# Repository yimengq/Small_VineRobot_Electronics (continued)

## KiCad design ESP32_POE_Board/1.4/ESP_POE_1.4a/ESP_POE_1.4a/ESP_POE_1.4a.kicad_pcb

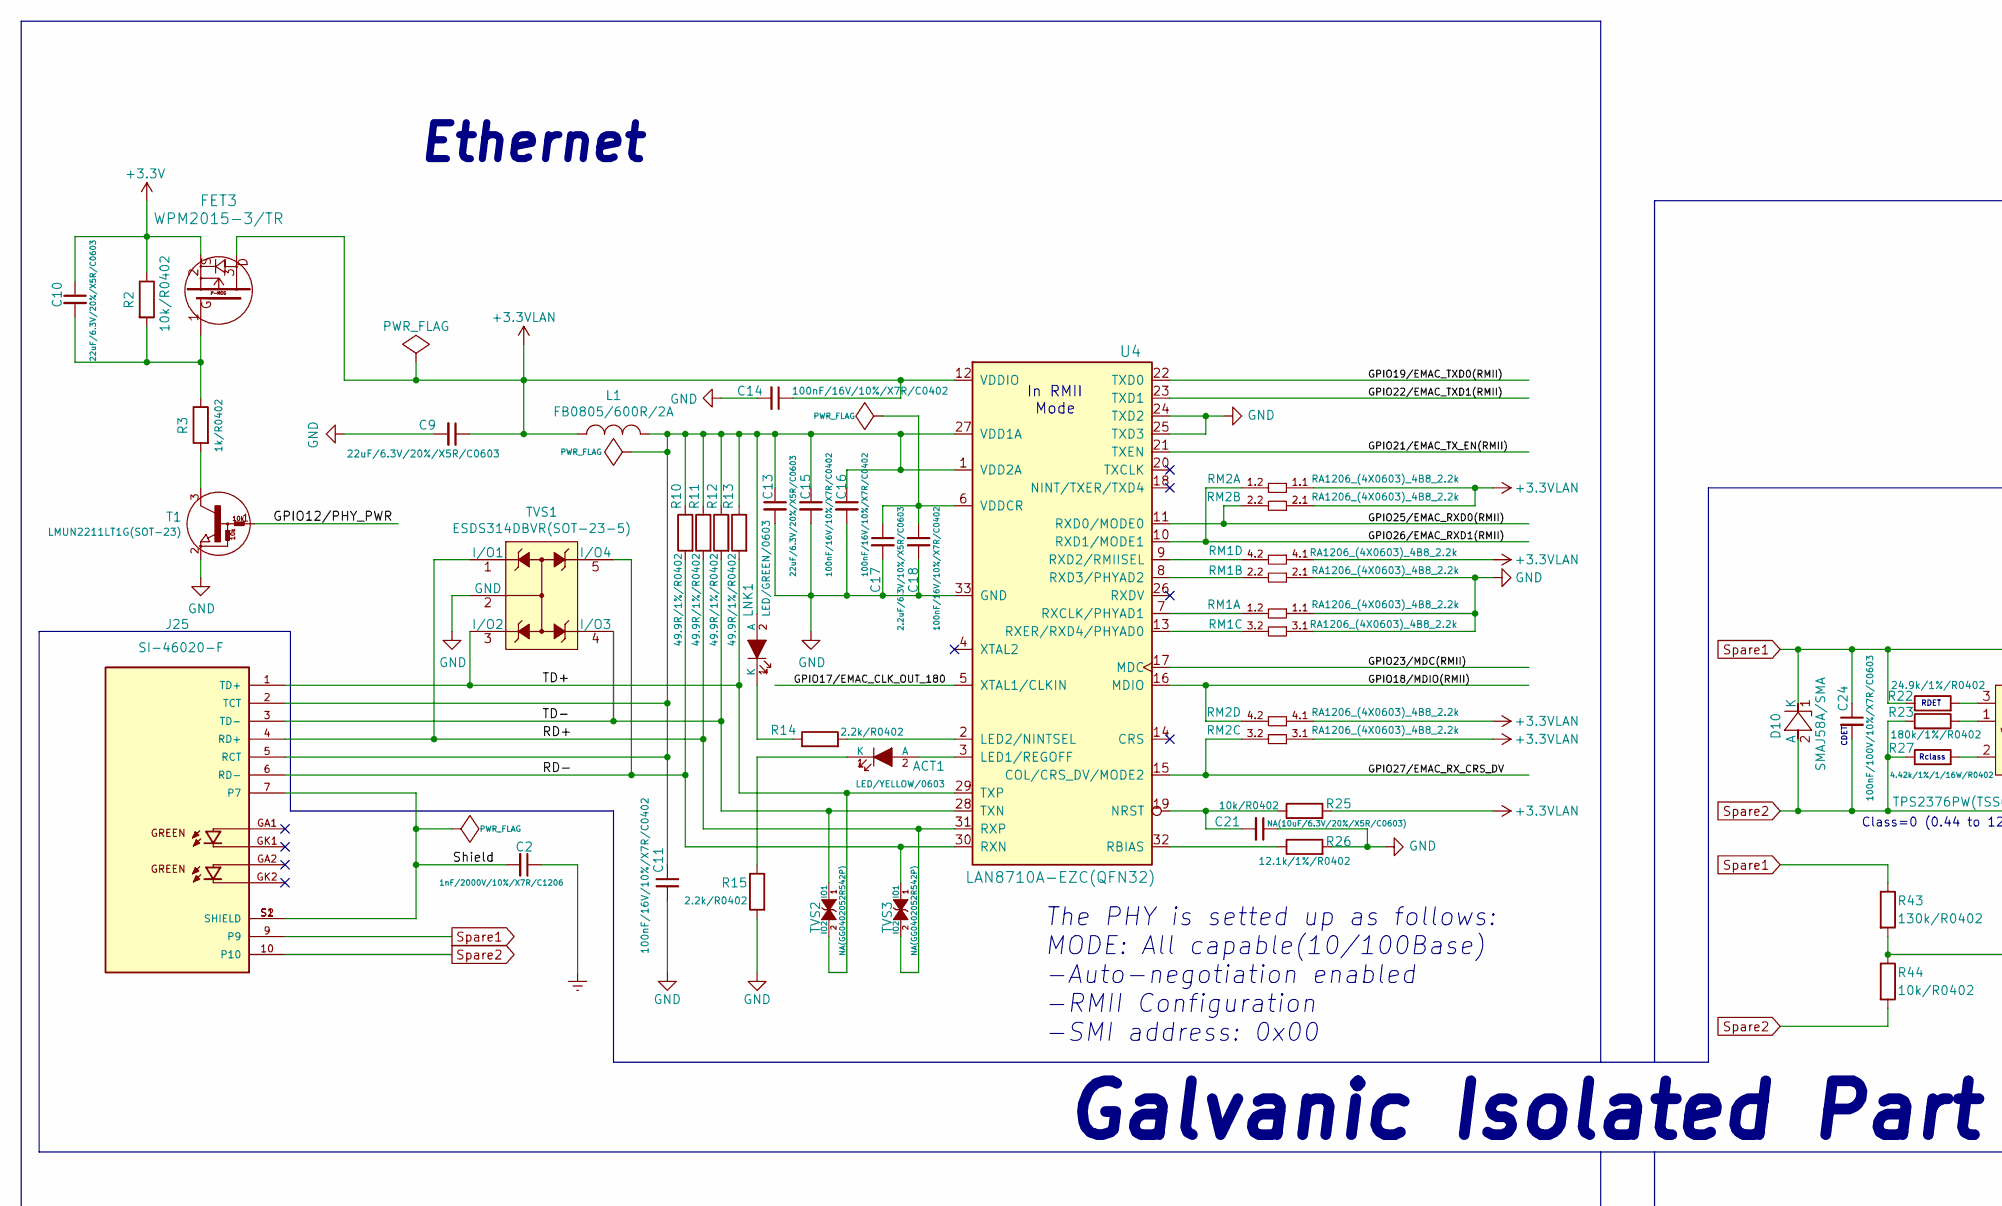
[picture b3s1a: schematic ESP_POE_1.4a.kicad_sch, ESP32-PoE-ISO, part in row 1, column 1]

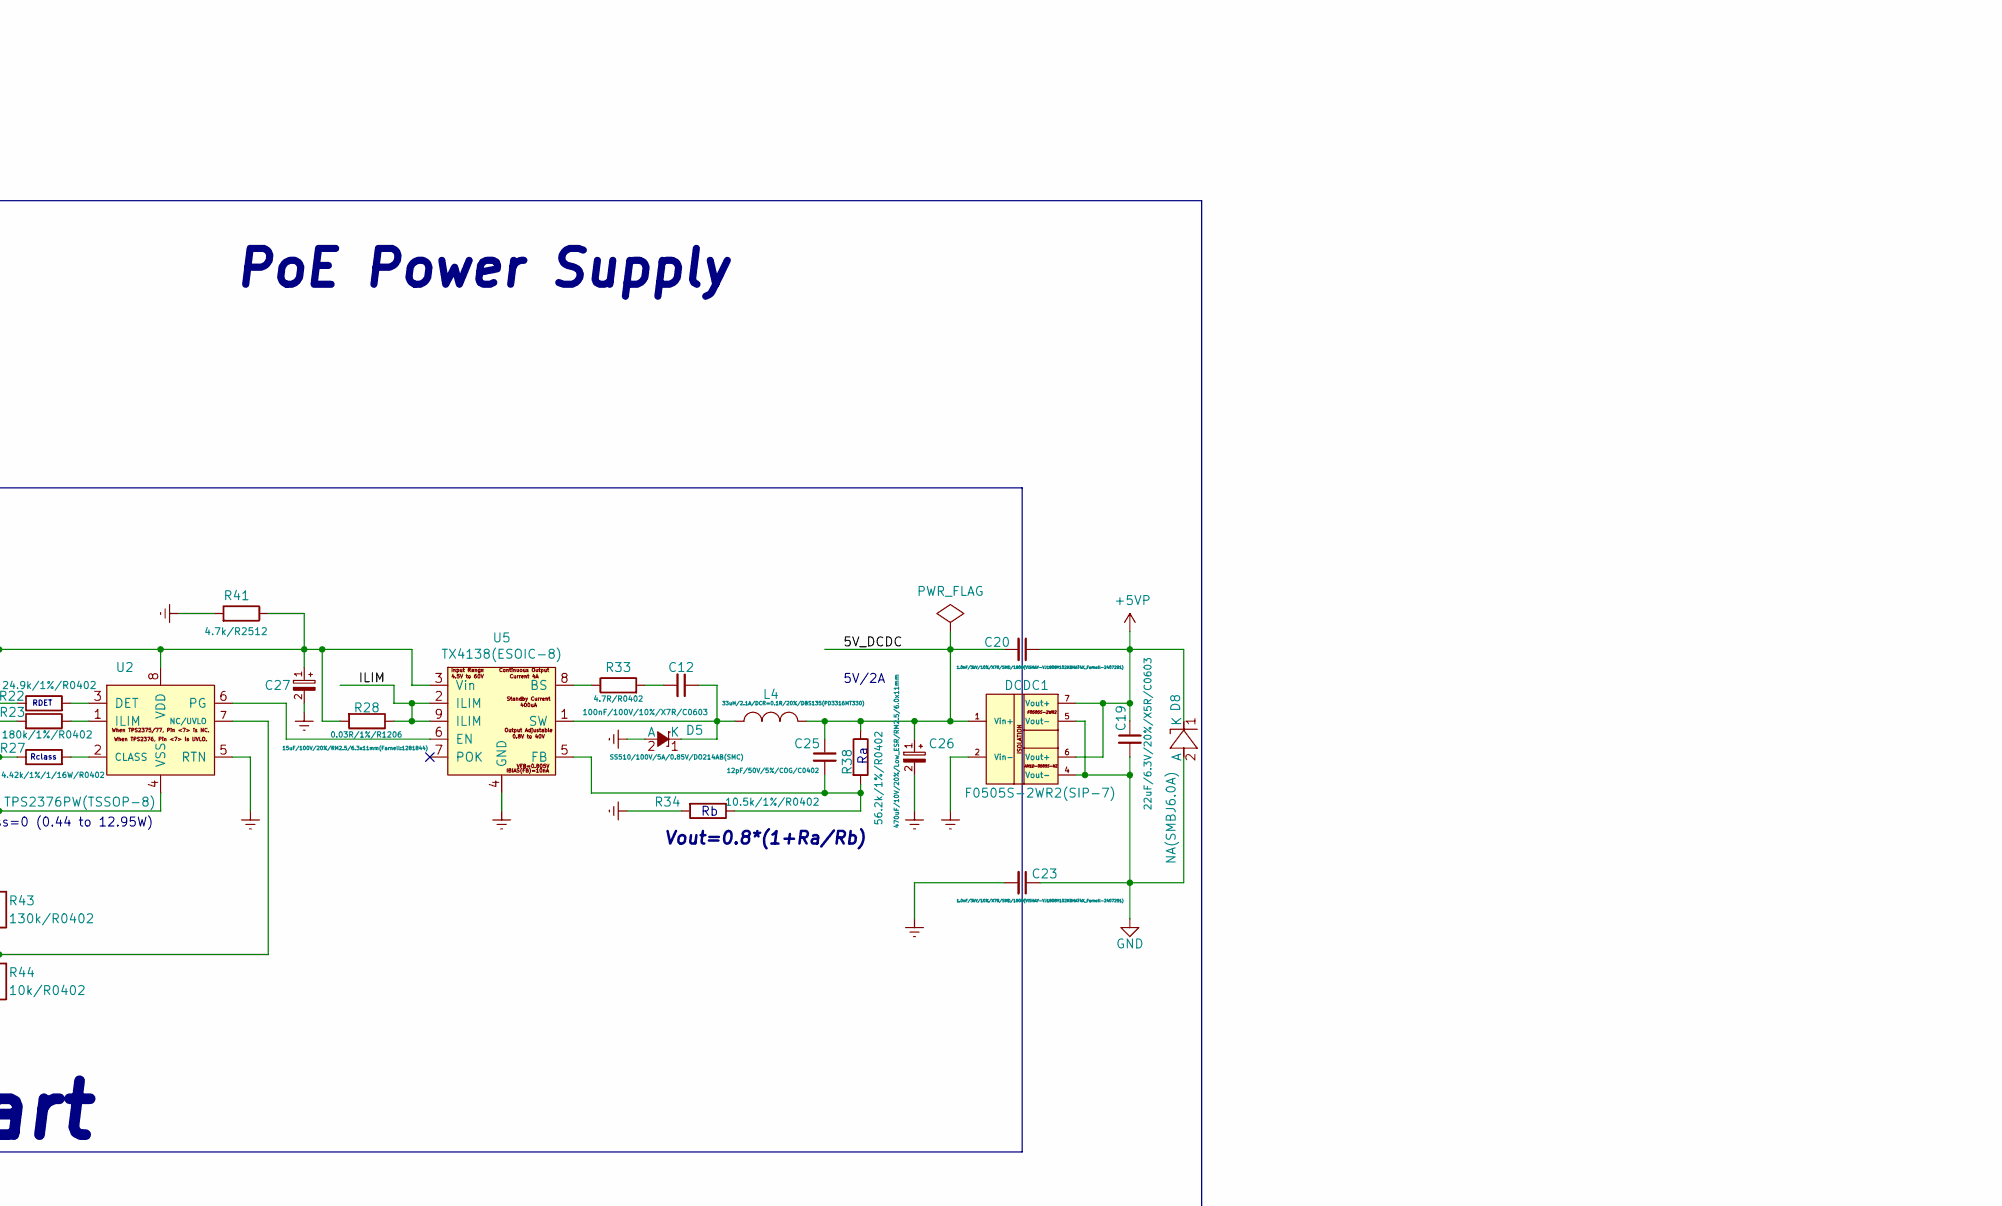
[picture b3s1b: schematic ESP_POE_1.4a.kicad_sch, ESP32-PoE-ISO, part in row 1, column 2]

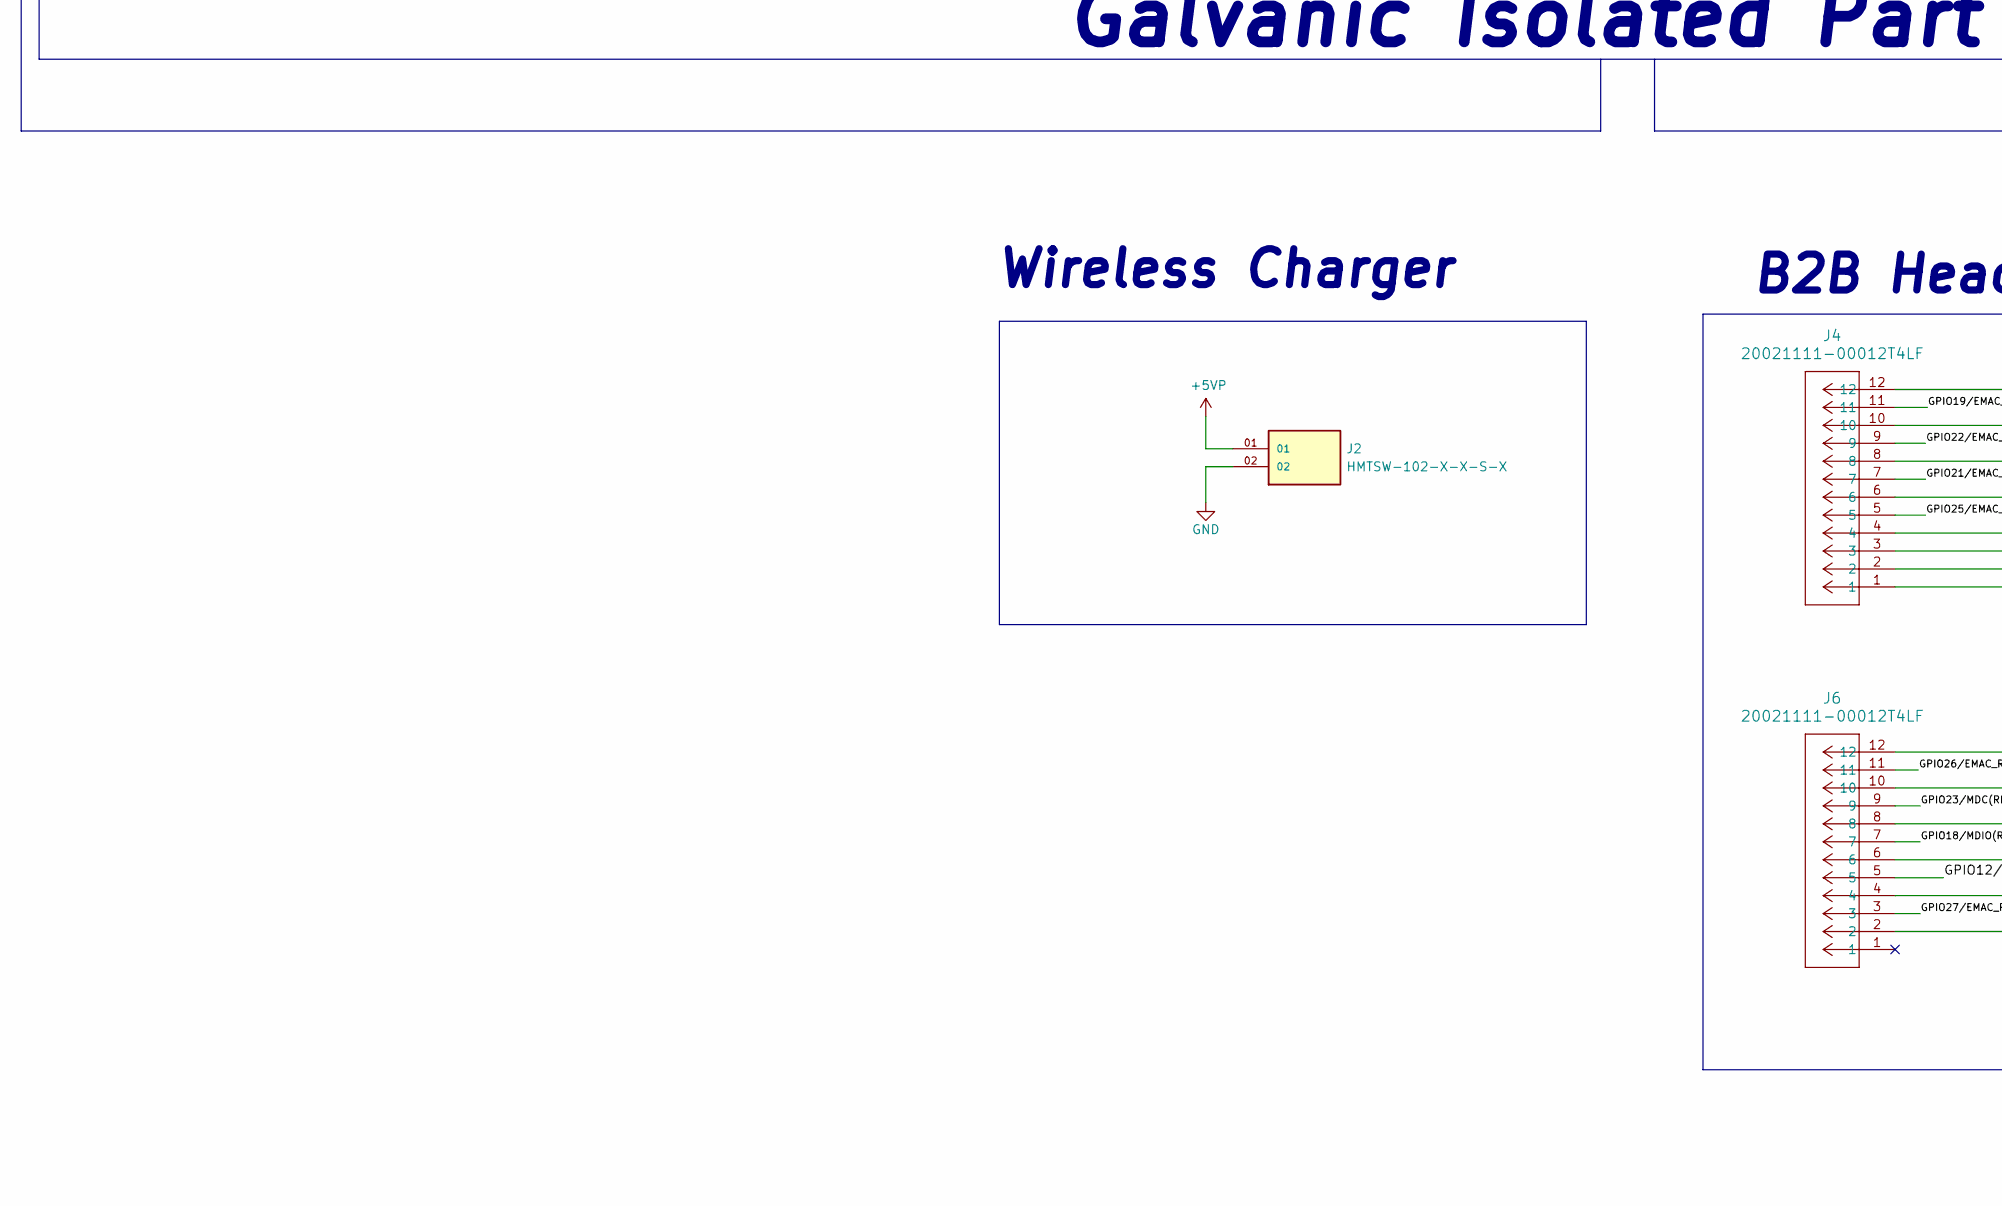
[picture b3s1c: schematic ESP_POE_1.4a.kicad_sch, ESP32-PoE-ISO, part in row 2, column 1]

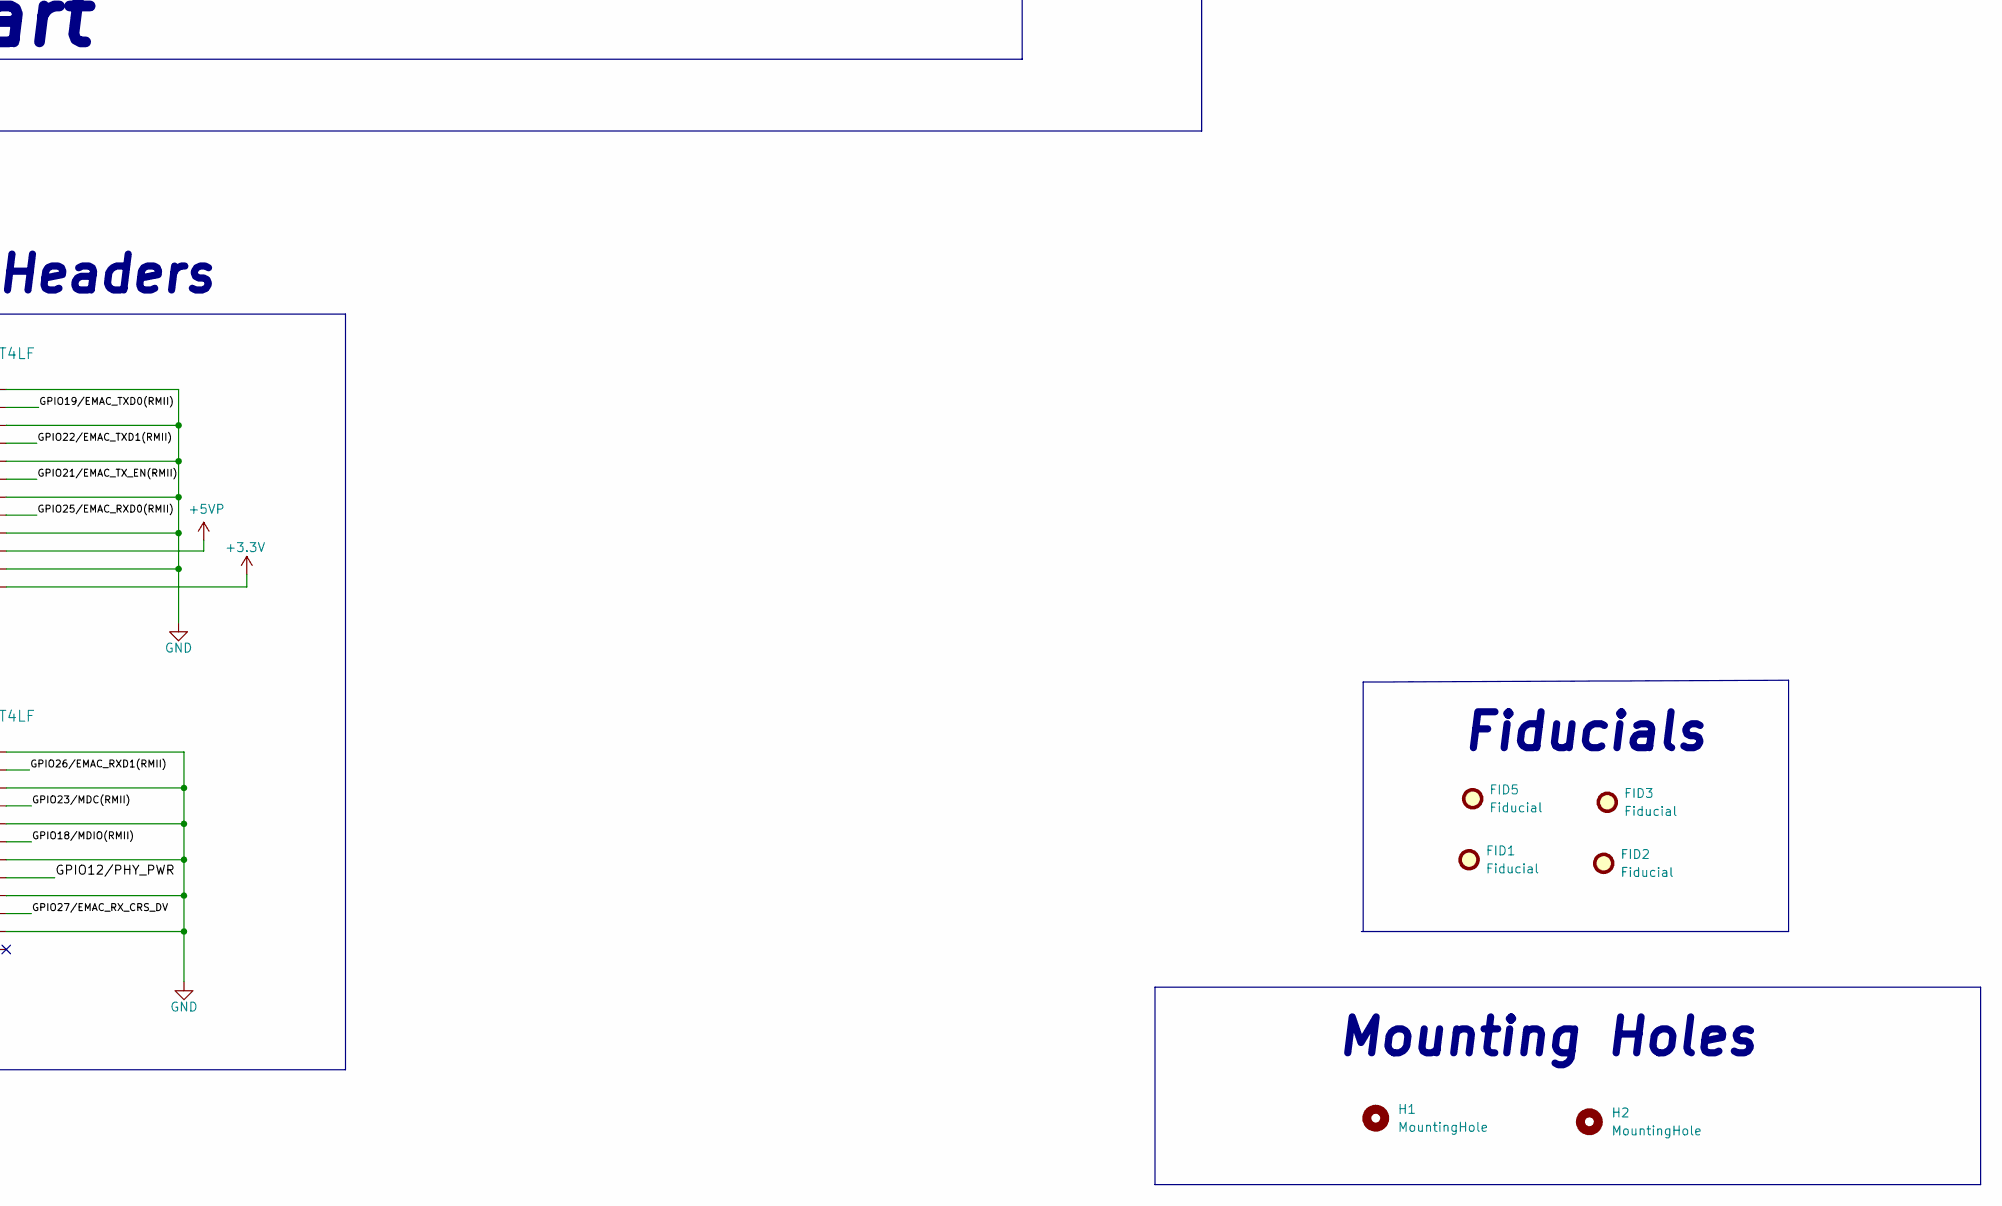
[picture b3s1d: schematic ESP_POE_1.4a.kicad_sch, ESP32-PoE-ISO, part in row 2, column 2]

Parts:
ACT1: LED/YELLOW/0603; LED_0603_KA; Mfr P/N 19-21/Y2C-CP1Q2B/4T
C2: 1nF/2000V/10%/X7R/C1206; C_1206_5MIL_DWS_ISO; Mfr P/N CC1206MKX7RDBB102
C9, C10, C13, C19: 22uF/6.3V/20%/X5R/C0603; C_0603_5MIL_DWS; Mfr P/N CL10A226MP8NUNE
C11, C14, C15, C16, C18: 100nF/16V/10%/X7R/C0402; C_0402_5MIL_DWS; Mfr P/N CC0402KRX7R7BB104
C12, C24: 100nF/100V/10%/X7R/C0603; C_0603_5MIL_DWS; Mfr P/N CC0603KRX7R9BB104
C17: 2.2uF/6.3V/10%/X5R/C0603; C_0603_5MIL_DWS; Mfr P/N CS1608X5R225K100NRB
C20, C23: 1.0nF/3kV/10%/X7R/SMD/1808(VISHAY-VJ1808Y102KBHAT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; C_1808(4520)_5MIL_DWS_ISO; Mfr P/N SCC1808X102K502TS
C21: NA(10uF/6.3V/20%/X5R/C0603); C_0603_5MIL_DWS; Mfr P/N CL10A106MA8NRNC
C25: 12pF/50V/5%/COG/C0402; C_0402_5MIL_DWS; Mfr P/N CL05C120JB51PNC
C26: 470uF/10V/20%/Low_ESR/RM2.5/6.0x11mm; CPOL-RM2.5mm_6.3x11mm_PTH; Mfr P/N GR477M016E12RR0EH4FP0
C27: 15uF/100V/20%/RM2.5/6.3x11mm(Farnell:1281844); CPOL-RM2.5mm_6.3x11mm_PTH; Mfr P/N EG22GM150F16OTMO
D5: SS510/100V/5A/0.85V/DO214AB(SMC); DO214AB(SMC)_1(K)-2(A); Mfr P/N SS510
D8: NA(SMBJ6.0A); DO214AA_1(K)-2(A)
D10: SMAJ58A/SMA; SMA-KA; Mfr P/N SMAJ58A-TR
DCDC1: F0505S-2WR2(SIP-7); SIP-7_Universal; Mfr P/N F0505S-2WR3
FET3: WPM2015-3/TR; SOT23; Mfr P/N WPM2015-3/TR
FID1, FID2, FID3, FID5: Fiducial; Fiducial_0.5mm_Mask1.5mm
H1, H2: MountingHole; MountingHole_2.1mm
J2: HMTSW-102-X-X-S-X; SAMTEC_HMTSW-102-X-X-S-X; PARTREV A
J4, J6: 20021111-00012T4LF; CONN_20021111-XX012XXLF_AMP; Mfr P/N DZ127R-11-09-25
J25: SI-46020-F; BEL_SI-46020-F; PARTREV C
L1: FB0805/600R/2A; L_0805_5MIL_DWS; Mfr P/N MH2029-601Y
L4: 33uH/2.1A/DCR=0.1R/20%/DBS135(PD3316MT330); IND_BOURNS_SRR1240; Mfr P/N SRR1240-330M
LNK1: LED/GREEN/0603; LED_0603_KA; Mfr P/N 18-225/R6G6C-A01/3T
R2, R25, R44: 10k/R0402; R_0402_5MIL_DWS; Mfr P/N RC0402FR-0710KL
R3: 1k/R0402; R_0402_5MIL_DWS; Mfr P/N RC0402FR-071KL
R10, R11, R12, R13: 49.9R/1%/R0402; R_0402_5MIL_DWS; Mfr P/N RC0402FR-0749R9P
R14, R15: 2.2k/R0402; R_0402_5MIL_DWS; Mfr P/N AC0402JR-072K2L
R22: 24.9k/1%/R0402; R_0402_5MIL_DWS
R23: 180k/1%/R0402; R_0402_5MIL_DWS
R26: 12.1k/1%/R0402; R_0402_5MIL_DWS
R27: 4.42k/1%/1/16W/R0402; R_0402_5MIL_DWS
R28: 0.03R/1%/R1206; R_1206_5MIL_DWS
R33: 4.7R/R0402; R_0402_5MIL_DWS
R34: 10.5k/1%/R0402; R_0402_5MIL_DWS
R38: 56.2k/1%/R0402; R_0402_5MIL_DWS
R41: 4.7k/R2512; R_2512_MM_DWS
R43: 130k/R0402; R_0402_5MIL_DWS
RM1, RM2: RA1206_(4X0603)_4B8_2.2k; R_MATRIX_4
T1: LMUN2211LT1G(SOT-23); SOT23
TVS1: ESDS314DBVR(SOT-23-5); SOT-23-5
TVS2, TVS3: NA(GG0402052R542P); D_0402_5MIL_DWS
U2: TPS2376PW(TSSOP-8); TSSOP-8_Pitch-0.65mm_Dimensions-4.40x3.00x1.20mm
U4: LAN8710A-EZC(QFN32); QFN32_EP(33)_5.00x5.00x0.90mm_Pitch_0.50mm
U5: TX4138(ESOIC-8); ESOIC-8

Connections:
+3.3VLAN: C9.1, C14.1, FET3.3, L1.1, R25.2, RM1.4.1, RM2.1.1, RM2.2.1, RM2.3.1, RM2.4.1, U4.12 (VDDIO)
+3V3: C10.1, FET3.2, J4.1, R2.1
+5VP: C19.1, C20.1, D8.1 (K), DCDC1.6 (Vout+), DCDC1.7 (Vout+), J2.01, J4.3; also elsewhere on the board
/5V_DCDC: C20.2, C25.1, C26.1 (+), DCDC1.1 (Vin+), L4.2, R38.1
/GPIO12/PHY_PWR: J6.5, T1.1 (B)
/GPIO17/EMAC_CLK_OUT_180: U4.5 (XTAL1/CLKIN)
/GPIO18/MDIO(RMII): J6.7, RM2.4.2, U4.16 (MDIO)
/GPIO19/EMAC_TXD0(RMII): J4.11, U4.22 (TXD0)
/GPIO21/EMAC_TX_EN(RMII): J4.7, U4.21 (TXEN)
/GPIO22/EMAC_TXD1(RMII): J4.9, U4.23 (TXD1)
/GPIO23/MDC(RMII): J6.9, U4.17 (MDC)
/GPIO25/EMAC_RXD0(RMII): J4.5, RM2.2.2, U4.11 (RXD0/MODE0)
/GPIO26/EMAC_RXD1(RMII): J6.11, RM2.1.2, U4.10 (RXD1/MODE1)
/GPIO27/EMAC_RX_CRS_DV: J6.3, RM2.3.2, U4.15 (COL/CRS_DV/MODE2)
/ILIM: R28.1, U5.2 (ILIM), U5.9 (ILIM)
/RD+: J2.4 (RD+), R11.2, TVS1.1 (I/O1), TVS3.2 (IO2), U4.31 (RXP)
/RD-: J2.6 (RD-), R10.2, TVS1.5 (I/O4), TVS3.1 (IO1), U4.30 (RXN)
/Shield: C2.2, J2.7, J2.S1 (SHIELD), J2.S2 (SHIELD)
/TD+: J2.1 (TD+), R13.2, TVS1.3 (I/O2), TVS2.2 (IO2), U4.29 (TXP)
/TD-: J2.3 (TD-), R12.2, TVS1.4 (I/O3), TVS2.1 (IO1), U4.28 (TXN)
Earth: C2.1, C23.2, C26.2 (-), C27.2 (-), D5.2 (A), DCDC1.2 (Vin-), R34.2, R41.2, U2.5 (RTN), U5.4 (GND)
GND: C9.2, C11.2, C13.2, C14.2, C15.2, C16.2, C17.2, C18.2, C19.2, C21.1, C23.1, D8.2 (A), DCDC1.4 (Vout-), DCDC1.5 (Vout-), J2.02, J4.2, J4.4, J4.6, J4.8, J4.10, J4.12, J6.2, J6.4, J6.6, J6.8, J6.10, J6.12, R15.2, R26.2, RM1.1.1, RM1.2.1, RM1.3.1, T1.2 (E), TVS1.2 (GND), U4.24 (TXD2), U4.25 (TXD3), U4.33 (GND); also elsewhere on the board
unnamed: ACT1.2 (A), U4.3 (LED1/REGOFF)
unnamed: ACT1.1 (K), R15.1
unnamed: C10.2, FET3.1, R2.2, R3.1
unnamed: C12.2, R33.2
unnamed: C12.1, D5.1 (K), L4.1, U5.1 (SW)
unnamed: C11.1, C13.1, C15.1, C16.1, J2.2 (TCT), J2.5 (RCT), L1.2, LNK1.2 (A), R10.1, R11.1, R12.1, R13.1, U4.1 (VDD2A), U4.27 (VDD1A)
unnamed: LNK1.1 (K), R14.1
unnamed: R3.2, T1.3 (C)
unnamed: R27.2, U2.2 (CLASS)
unnamed: R22.2, U2.3 (DET)
unnamed: R23.1, U2.1 (ILIM)
unnamed: R43.2, R44.1, U2.7 (NC/UVLO)
unnamed: U2.6 (PG), U5.6 (EN)
unnamed: R14.2, U4.2 (LED2/NINTSEL)
unnamed: C21.2, R25.1, U4.19 (NRST)
unnamed: R26.1, U4.32 (RBIAS)
unnamed: RM1.1.2, U4.7 (RXCLK/PHYAD1)
unnamed: RM1.4.2, U4.9 (RXD2/RMIISEL)
unnamed: RM1.2.2, U4.8 (RXD3/PHYAD2)
unnamed: RM1.3.2, U4.13 (RXER/RXD4/PHYAD0)
unnamed: C17.1, C18.1, U4.6 (VDDCR)
unnamed: R33.1, U5.8 (BS)
unnamed: C25.2, R34.1, R38.2, U5.5 (FB)
Spare1: C24.1, C27.1 (+), D10.1 (K), J2.9, R22.1, R28.2, R41.1, R43.1, U2.8 (VDD), U5.3 (Vin)
Spare2: C24.2, D10.2 (A), J2.10, R23.2, R27.1, R44.2, U2.4 (VSS)

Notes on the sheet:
5V/2A
In RMII Mode
PoE Power Supply
Ethernet
B2B Headers
Class=0 (0.44 to 12.95W)
CDET
The PHY is setted up as follows: MODE: All capable(10/100Base) -Auto-negotiation enabled -RMII Configuration -SMI address: 0x00
Galvanic Isolated Part
Rclass
Vout=0.8*(1+Ra/Rb)
Mounting Holes
Fiducials
RDET
Wireless Charger

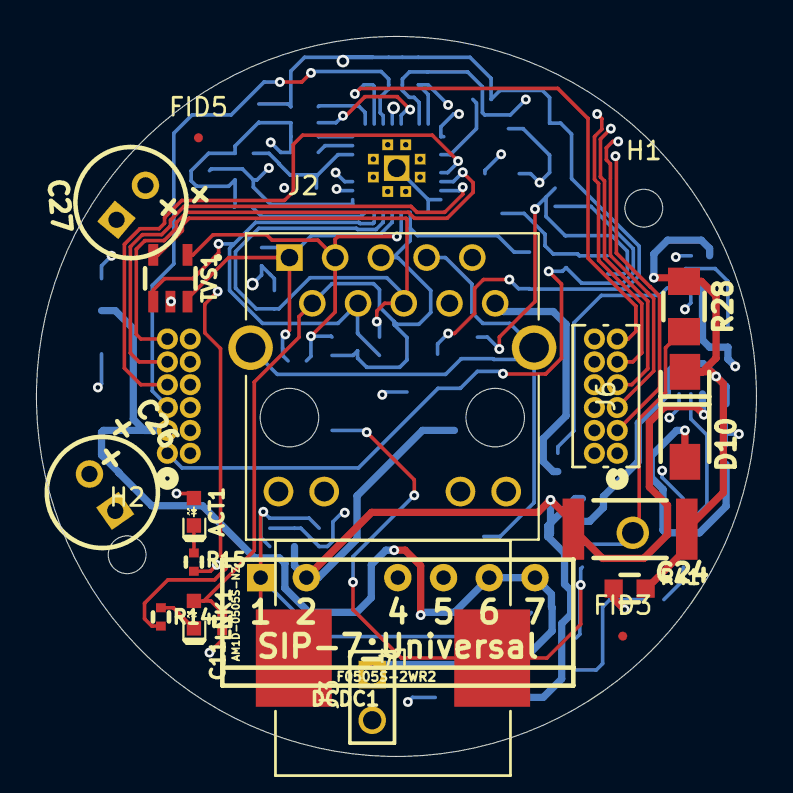
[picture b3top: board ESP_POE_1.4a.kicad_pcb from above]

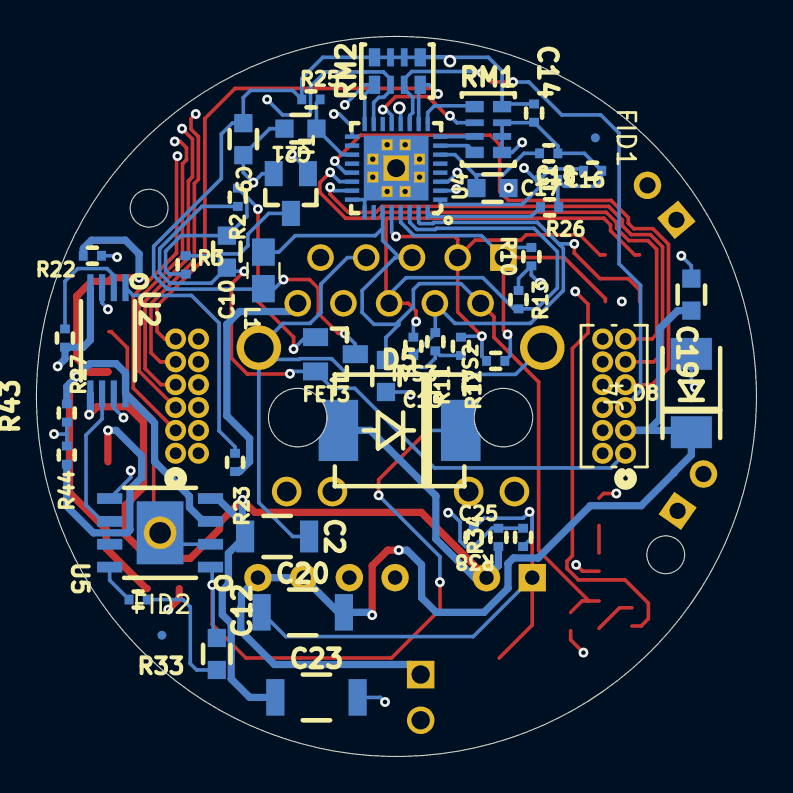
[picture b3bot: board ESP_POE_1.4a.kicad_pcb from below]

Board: 4 copper layers, 40.0 x 40.0 mm, 67 parts (46 on the bottom side), 46 nets.

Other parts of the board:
J3: HMTSW-102-X-X-S-X; SAMTEC_HMTSW-102-X-X-S-X

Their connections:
+5VP: J3.01; also elsewhere on the board
GND: J3.02; also elsewhere on the board

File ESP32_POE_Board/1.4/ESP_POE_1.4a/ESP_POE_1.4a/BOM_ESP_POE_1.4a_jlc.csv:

Comment,Designator,Footprint,JLCPCB Part #_optional_
LED/YELLOW/0603,ACT1,OLIMEX_LEDs-FP:LED_0603_KA,C2986008
1nF/2000V/10%/X7R/C1206,C2,OLIMEX_RLC-FP:C_1206_5MIL_DWS_ISO,C527363
22uF/6.3V/20%/X5R/C0603,"C9, C10, C13, C19",OLIMEX_RLC-FP:C_0603_5MIL_DWS,C86295
100nF/16V/10%/X7R/C0402,"C11, C14-C16, C18",OLIMEX_RLC-FP:C_0402_5MIL_DWS,C60474
100nF/100V/10%/X7R/C0603,"C12, C24",OLIMEX_RLC-FP:C_0603_5MIL_DWS,C14663
2.2uF/6.3V/10%/X5R/C0603,C17,OLIMEX_RLC-FP:C_0603_5MIL_DWS,C5189830
1.0nF/3kV/10%/X7R/SMD/1808(VISHAY-VJ1808Y102KBHAT4X_Farnell-2407291),"C20, C23",OLIMEX_RLC-FP:C_1808(4520)_5MIL_DWS_ISO,C2939745
NA(10uF/6.3V/20%/X5R/C0603),C21,OLIMEX_RLC-FP:C_0603_5MIL_DWS,C96446
12pF/50V/5%/COG/C0402,C25,OLIMEX_RLC-FP:C_0402_5MIL_DWS,C472446
470uF/10V/20%/Low_ESR/RM2.5/6.0x11mm,C26,OLIMEX_RLC-FP:CPOL-RM2.5mm_6.3x11mm_PTH,C3039776
15uF/100V/20%/RM2.5/6.3x11mm(Farnell:1281844),C27,OLIMEX_RLC-FP:CPOL-RM2.5mm_6.3x11mm_PTH,C2841644
SS510/100V/5A/0.85V/DO214AB(SMC),D5,OLIMEX_Diodes-FP:DO214AB(SMC)_1(K)-2(A),C5339843
SMAJ58A/SMA,D10,OLIMEX_Diodes-FP:SMA-KA,C132936
F0505S-2WR2(SIP-7),DCDC1,OLIMEX_Regulators-FP:SIP-7_Universal,C7598643
WPM2015-3/TR,FET3,OLIMEX_Transistors-FP:SOT23,C6562215
HMTSW-102-X-X-S-X,J3,HMTSW-102-X-X-S-X:SAMTEC_HMTSW-102-X-X-S-X,C234182
C3324132,"J4, J6",CONN_20021111-XX012XXLF_AMP,C3324132
FB0805/600R/2A,L1,OLIMEX_RLC-FP:L_0805_5MIL_DWS,C2661781
LED/GREEN/0603,LNK1,OLIMEX_LEDs-FP:LED_0603_KA,C172883
10k/R0402,"R2, R25, R44",OLIMEX_RLC-FP:R_0402_5MIL_DWS,C60490
1k/R0402,R3,OLIMEX_RLC-FP:R_0402_5MIL_DWS,C106235
49.9R/1%/R0402,R10-R13,OLIMEX_RLC-FP:R_0402_5MIL_DWS,C851839
2.2k/R0402,"R14, R15",OLIMEX_RLC-FP:R_0402_5MIL_DWS,C144718
24.9k/1%/R0402,R22,OLIMEX_RLC-FP:R_0402_5MIL_DWS,C852664
180k/1%/R0402,R23,OLIMEX_RLC-FP:R_0402_5MIL_DWS,C144794
12.1k/1%/R0402,R26,OLIMEX_RLC-FP:R_0402_5MIL_DWS,C281773
4.42k/1%/1/16W/R0402,R27,OLIMEX_RLC-FP:R_0402_5MIL_DWS,C513571
0.03R/1%/R1206,R28,OLIMEX_RLC-FP:R_1206_5MIL_DWS,C375524
4.7R/R0402,R33,OLIMEX_RLC-FP:R_0402_5MIL_DWS,C137962
10.5k/1%/R0402,R34,OLIMEX_RLC-FP:R_0402_5MIL_DWS,C171695
56.2k/1%/R0402,R38,OLIMEX_RLC-FP:R_0402_5MIL_DWS,C227142
4.7k/R2512,R41,OLIMEX_RLC-FP:R_2512_MM_DWS,C163339
130k/R0402,R43,OLIMEX_RLC-FP:R_0402_5MIL_DWS,C852515
RA1206_(4X0603)_4B8_2.2k,"RM1, RM2",OLIMEX_RLC-FP:R_MATRIX_4,C12001
LMUN2211LT1G(SOT-23),T1,OLIMEX_Transistors-FP:SOT23,C12775
ESDS314DBVR(SOT-23-5),TVS1,OLIMEX_Diodes-FP:SOT-23-5,C1847859
TPS2376PW(TSSOP-8),U2,OLIMEX_IC-FP:TSSOP-8_Pitch-0.65mm_Dimensions-4.40x3.00x1.20mm,C544899
LAN8710A-EZC(QFN32),U4,OLIMEX_IC-FP:QFN32_EP(33)_5.00x5.00x0.90mm_Pitch_0.50mm,C46185
TX4138(ESOIC-8),U5,OLIMEX_Regulators-FP:ESOIC-8,C329267
